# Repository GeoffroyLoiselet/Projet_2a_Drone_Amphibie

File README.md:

# Projet_2a_Drone_Amphibie
Projet drone amphibie ENSEA 2ème année

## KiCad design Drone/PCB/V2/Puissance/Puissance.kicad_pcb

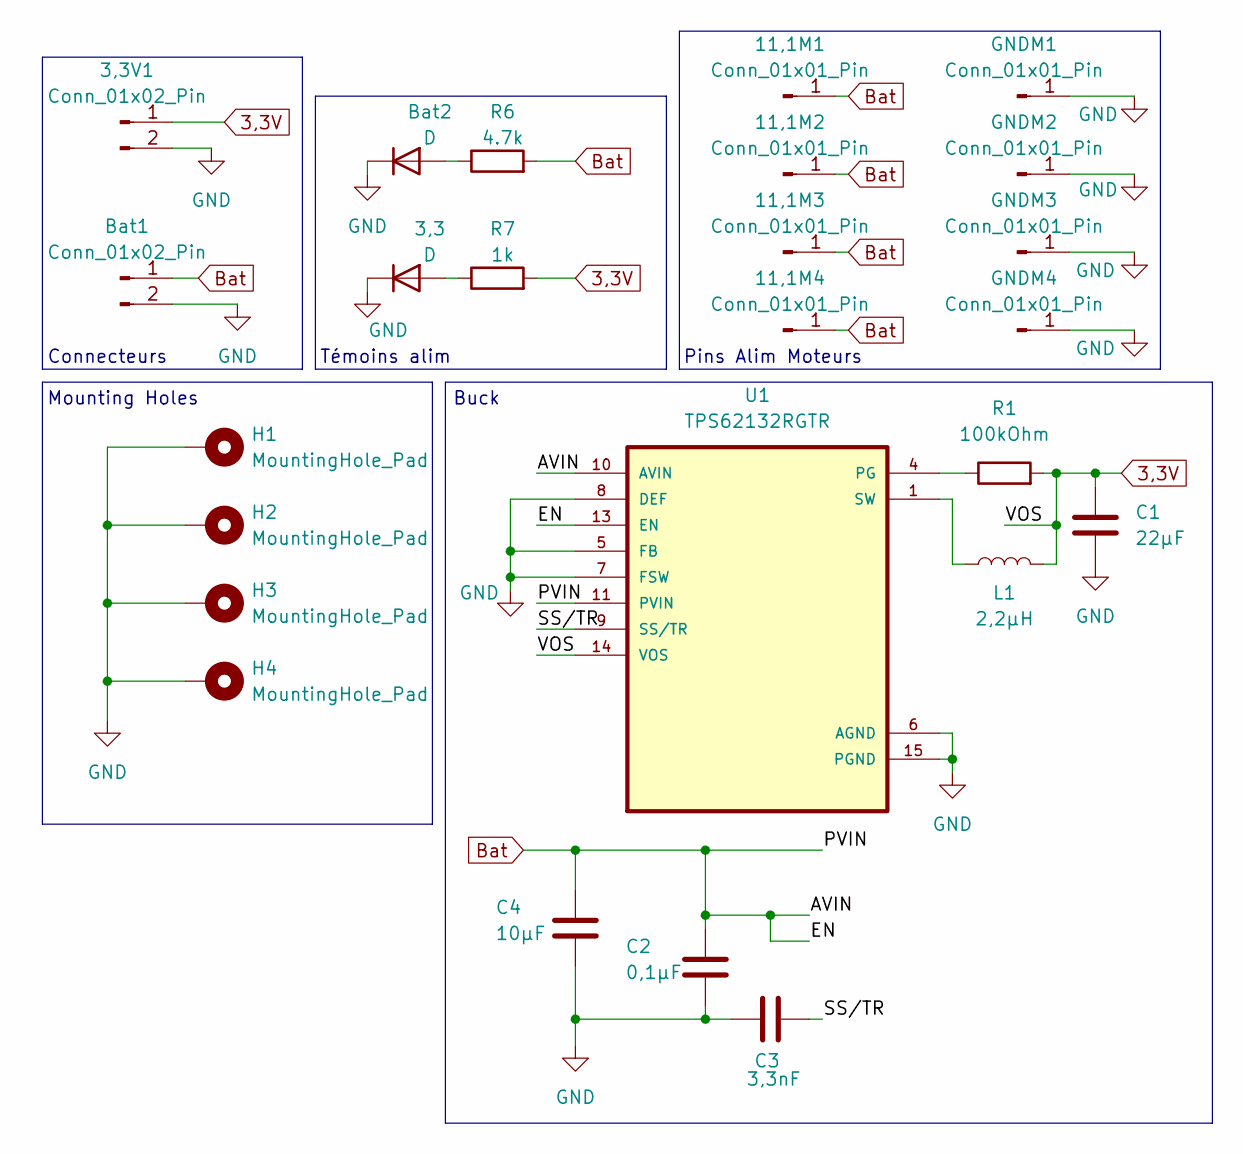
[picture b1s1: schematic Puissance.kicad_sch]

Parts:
3,3: D; D_0603_1608Metric_Pad1.05x0.95mm_HandSolder
3,3V1: Conn_01x02_Pin; PinSocket_1x02_P2.54mm_Vertical
11,1M1, 11,1M2, 11,1M3, 11,1M4: Conn_01x01_Pin; SolderWire-1.5sqmm_1x01_D1.7mm_OD3mm
Bat1: Conn_01x02_Pin; SolderWire-1.5sqmm_1x02_P6mm_D1.7mm_OD3mm
Bat2: D; D_0603_1608Metric_Pad1.05x0.95mm_HandSolder
C1: 22µF; C_0603_1608Metric_Pad1.08x0.95mm_HandSolder
C2: 0,1µF; C_0603_1608Metric_Pad1.08x0.95mm_HandSolder
C3: 3,3nF; C_0603_1608Metric_Pad1.08x0.95mm_HandSolder
C4: 10µF; C_0603_1608Metric_Pad1.08x0.95mm_HandSolder
GNDM1, GNDM2, GNDM3, GNDM4: Conn_01x01_Pin; SolderWire-1.5sqmm_1x01_D1.7mm_OD3mm
H1, H2, H3, H4: MountingHole_Pad; MountingHole_3.2mm_M3_DIN965_Pad
L1: 2,2µH; L_0603_1608Metric_Pad1.05x0.95mm_HandSolder
R1: 100kOhm; R_0201_0603Metric_Pad0.64x0.40mm_HandSolder
R6: 4.7k; R_0603_1608Metric_Pad0.98x0.95mm_HandSolder
R7: 1k; R_0603_1608Metric_Pad0.98x0.95mm_HandSolder
U1: TPS62132RGTR; VQFN-16-1EP_3x3mm_P0.5mm_EP1.1x1.1mm_ThermalVias

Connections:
3,3V: 3,3V1.1, C1.1, L1.2, R1.2, R7.2, U1.14 (VOS)
/SS/TR: C3.2, U1.9 (SS/TR)
Bat: 11,1M1.1, 11,1M2.1, 11,1M3.1, 11,1M4.1, Bat1.1, C2.1, C4.1, R6.2, U1.10 (AVIN), U1.11 (PVIN), U1.12 (PVIN), U1.13 (EN)
GND: 3,3.1 (K), 3,3V1.2, Bat1.2, Bat2.1 (K), C1.2, C2.2, C3.1, C4.2, GNDM1.1, GNDM2.1, GNDM3.1, GNDM4.1, H1.1, H2.1, H3.1, H4.1, U1.5 (FB), U1.6 (AGND), U1.7 (FSW), U1.8 (DEF), U1.15 (PGND), U1.16 (PGND), U1.17 (PGND)
unnamed: 3,3.2 (A), R7.1
unnamed: Bat2.2 (A), R6.1
unnamed: L1.1, U1.1 (SW), U1.2 (SW), U1.3 (SW)
unnamed: R1.1, U1.4 (PG)

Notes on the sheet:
Pins Alim Moteurs
Connecteurs
Buck
Mounting Holes
Témoins alim

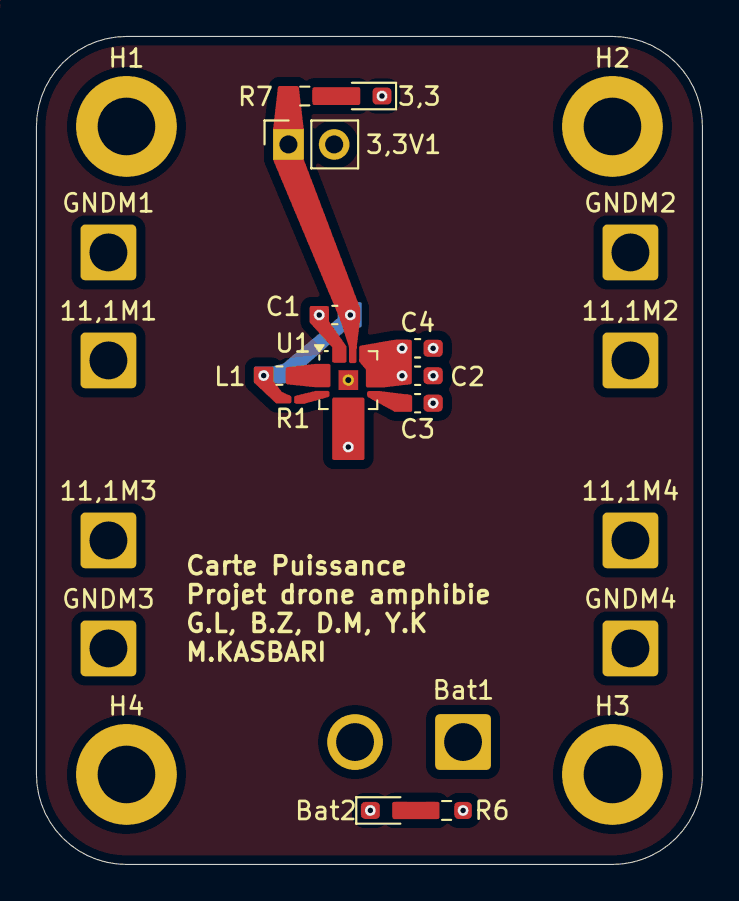
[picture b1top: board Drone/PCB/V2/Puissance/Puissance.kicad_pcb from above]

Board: 4 copper layers, 37.0 x 46.0 mm, 25 parts (0 on the bottom side), 8 nets.

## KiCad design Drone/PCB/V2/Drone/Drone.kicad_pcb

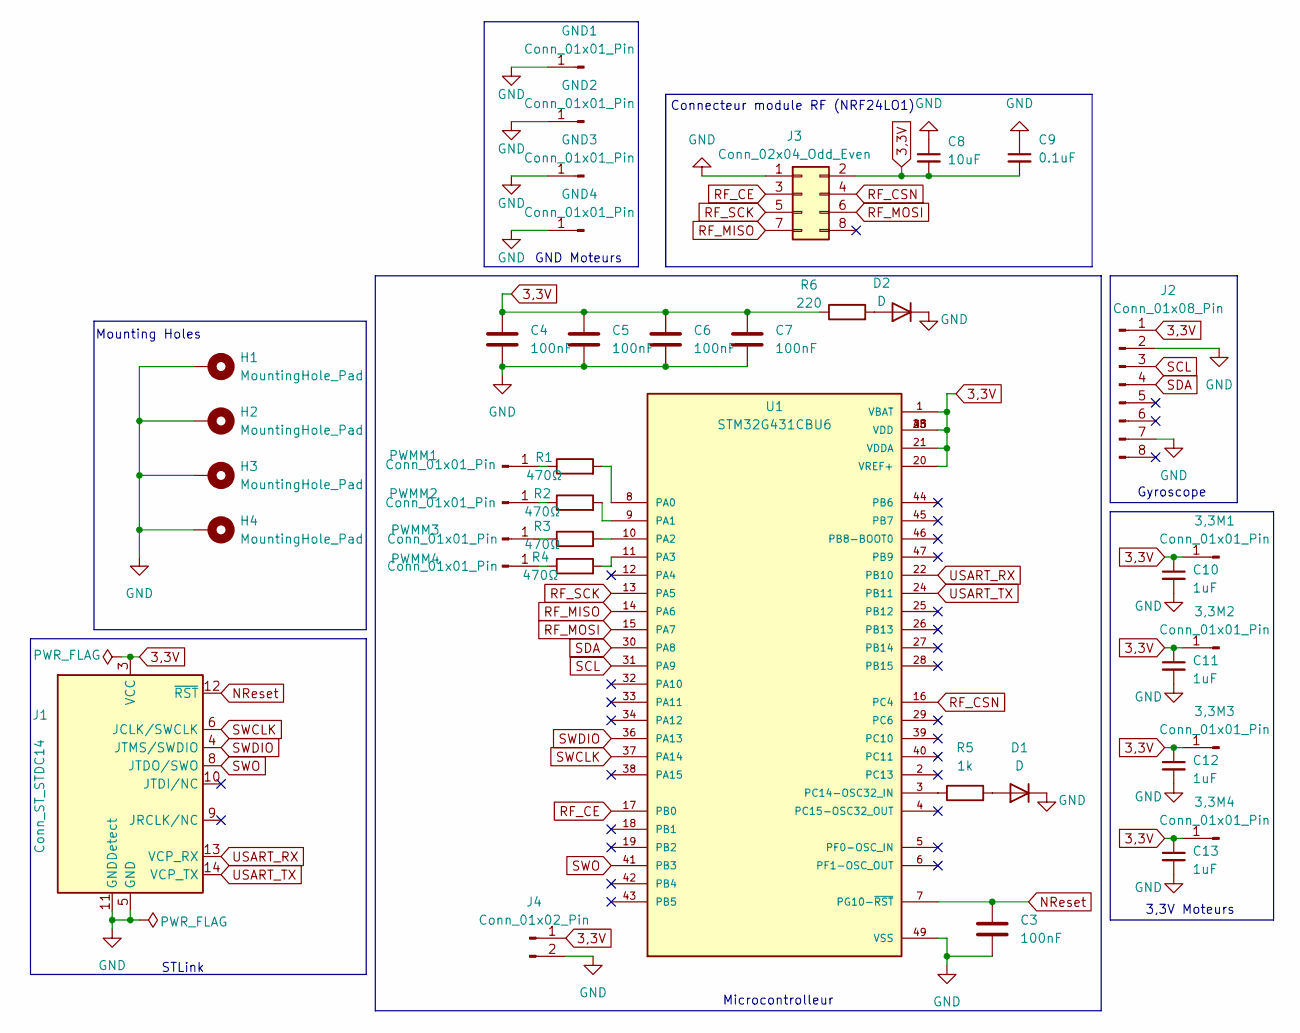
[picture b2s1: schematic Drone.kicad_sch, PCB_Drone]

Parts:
3,3M1, 3,3M2, 3,3M3, 3,3M4: Conn_01x01_Pin; SolderWire-0.75sqmm_1x01_D1.25mm_OD2.3mm
C3, C4, C5, C6, C7: 100nF; C_0603_1608Metric_Pad1.08x0.95mm_HandSolder
C8: 10uF; C_0603_1608Metric_Pad1.08x0.95mm_HandSolder
C9: 0.1uF; C_0603_1608Metric_Pad1.08x0.95mm_HandSolder
C10, C11, C12, C13: 1uF; C_0603_1608Metric_Pad1.08x0.95mm_HandSolder
D1, D2: D; D_0603_1608Metric_Pad1.05x0.95mm_HandSolder
GND1, GND2, GND3, GND4: Conn_01x01_Pin; SolderWire-0.75sqmm_1x01_D1.25mm_OD2.3mm
H1, H2, H3, H4: MountingHole_Pad; MountingHole_3.2mm_M3_DIN965_Pad
J1: Conn_ST_STDC14; PinHeader_2x07_P1.27mm_Vertical_SMD
J2: Conn_01x08_Pin; PinSocket_1x08_P1.00mm_Vertical
J3: Conn_02x04_Odd_Even; JST_PHD_B8B-PHDSS_2x04_P2.00mm_Vertical
J4: Conn_01x02_Pin; PinSocket_1x02_P2.54mm_Vertical
PWMM1, PWMM2, PWMM3, PWMM4: Conn_01x01_Pin; SolderWire-0.75sqmm_1x01_D1.25mm_OD2.3mm
R1, R2, R3, R4: 470Ω; R_0603_1608Metric_Pad0.98x0.95mm_HandSolder
R5: 1k; R_0603_1608Metric_Pad0.98x0.95mm_HandSolder
R6: 220; R_0603_1608Metric_Pad0.98x0.95mm_HandSolder
U1: STM32G431CBU6; QFN50P700X700X60-49N; PARTREV 6

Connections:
3,3V: 3,3M1.1, 3,3M2.1, 3,3M3.1, 3,3M4.1, C4.1, C5.1, C6.1, C7.1, C8.2, C9.2, C10.1, C11.1, C12.1, C13.1, J1.3 (VCC), J2.1, J3.2, J4.1, R6.1, U1.1 (VBAT), U1.20 (VREF+), U1.21 (VDDA), U1.23 (VDD), U1.35 (VDD), U1.48 (VDD)
GND: C3.2, C4.2, C5.2, C6.2, C7.2, C8.1, C9.1, C10.2, C11.2, C12.2, C13.2, D1.1 (K), D2.1 (K), GND1.1, GND2.1, GND3.1, GND4.1, H1.1, H2.1, H3.1, H4.1, J1.5 (GND), J1.7 (GND), J1.11 (GNDDetect), J2.2, J2.7, J3.1, J4.2, U1.49 (VSS)
NReset: C3.1, J1.12 (~RST), U1.7 (PG10-~RST)
unnamed: D1.2 (A), R5.2
unnamed: D2.2 (A), R6.2
unnamed: PWMM1.1, R1.1
unnamed: PWMM2.1, R2.1
unnamed: PWMM3.1, R3.1
unnamed: PWMM4.1, R4.1
unnamed: R1.2, U1.8 (PA0)
unnamed: R2.2, U1.9 (PA1)
unnamed: R3.2, U1.10 (PA2)
unnamed: R4.2, U1.11 (PA3)
unnamed: R5.1, U1.3 (PC14-OSC32_IN)
RF_CE: J3.3, U1.17 (PB0)
RF_CSN: J3.4, U1.16 (PC4)
RF_MISO: J3.7, U1.14 (PA6)
RF_MOSI: J3.6, U1.15 (PA7)
RF_SCK: J3.5, U1.13 (PA5)
SCL: J2.3, U1.31 (PA9)
SDA: J2.4, U1.30 (PA8)
SWCLK: J1.6 (JCLK/SWCLK), U1.37 (PA14)
SWDIO: J1.4 (JTMS/SWDIO), U1.36 (PA13)
SWO: J1.8 (JTDO/SWO), U1.41 (PB3)
USART_RX: J1.13 (VCP_RX), U1.22 (PB10)
USART_TX: J1.14 (VCP_TX), U1.24 (PB11)

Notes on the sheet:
3,3V Moteurs
Connecteur module RF (NRF24LO1)
Microcontrolleur
Gyroscope
STLink
Mounting Holes
GND Moteurs

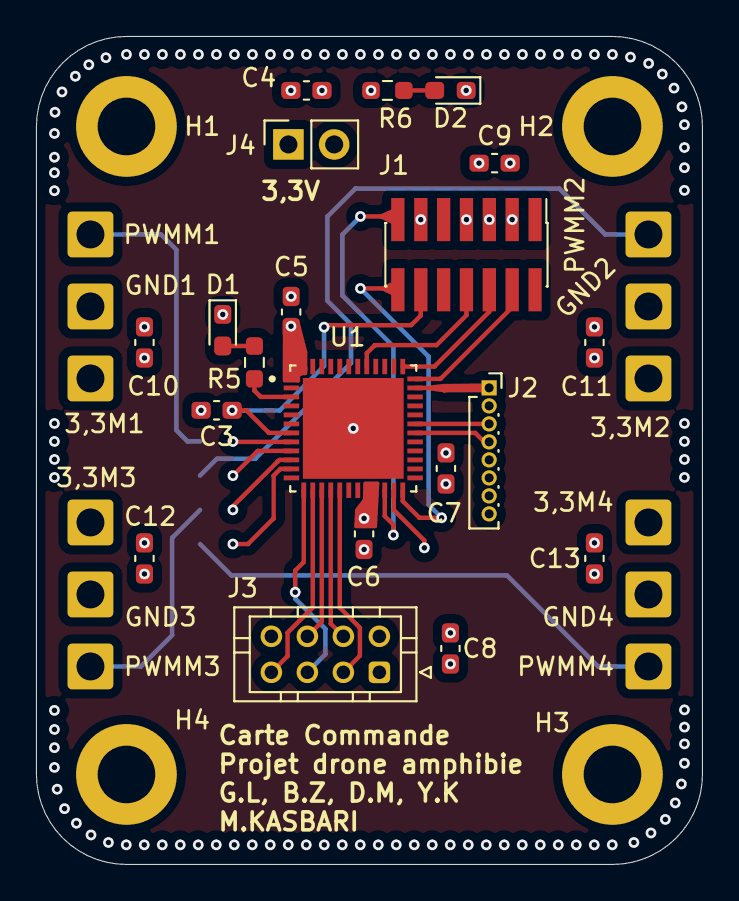
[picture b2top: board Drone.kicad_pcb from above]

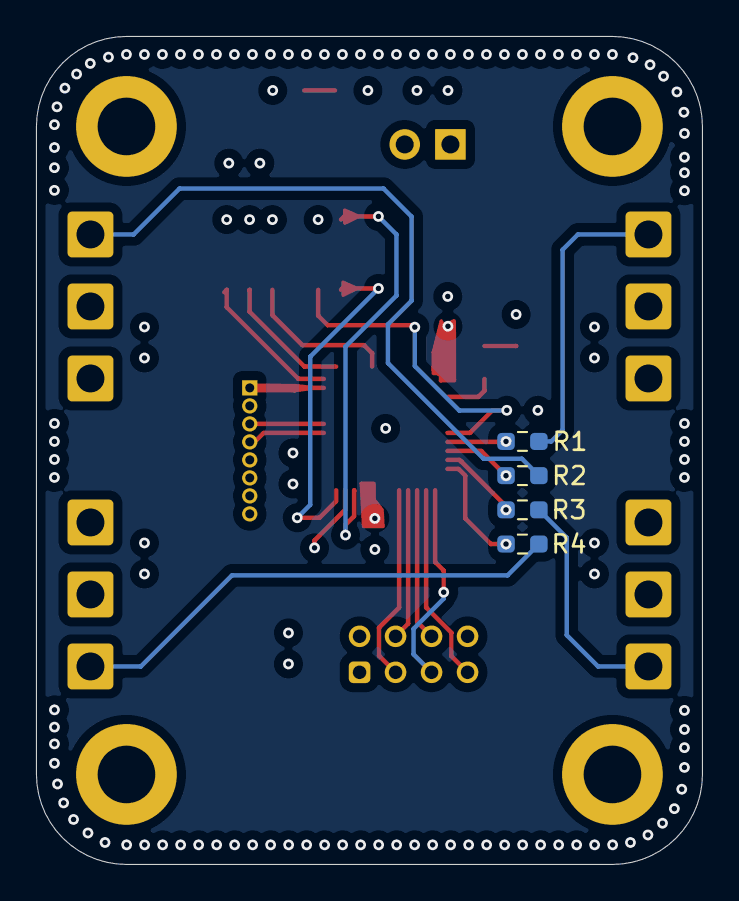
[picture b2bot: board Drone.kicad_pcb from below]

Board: 4 copper layers, 37.0 x 46.0 mm, 40 parts (4 on the bottom side), 26 nets.

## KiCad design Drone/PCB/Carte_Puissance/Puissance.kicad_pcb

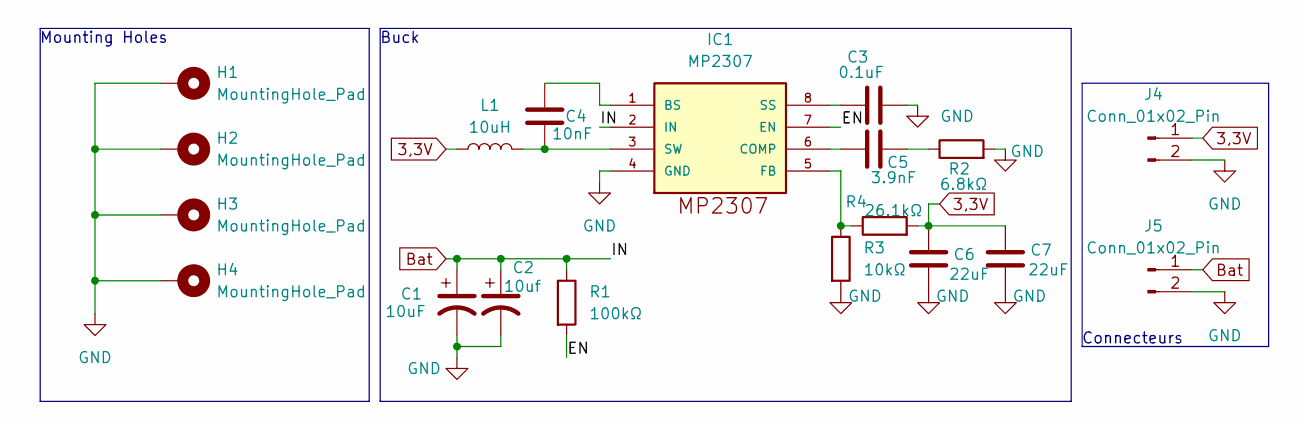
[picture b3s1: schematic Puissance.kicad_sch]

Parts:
C1: 10uF; C_0603_1608Metric_Pad1.08x0.95mm_HandSolder
C2: 10uf; C_0603_1608Metric_Pad1.08x0.95mm_HandSolder
C3: 0.1uF; C_0603_1608Metric_Pad1.08x0.95mm_HandSolder
C4: 10nF; C_0603_1608Metric_Pad1.08x0.95mm_HandSolder
C5: 3.9nF; C_0603_1608Metric_Pad1.08x0.95mm_HandSolder
C6, C7: 22uF; C_0603_1608Metric_Pad1.08x0.95mm_HandSolder
H1, H2, H3, H4: MountingHole_Pad; MountingHole_3.2mm_M3_DIN965_Pad
IC1: MP2307; MP2307DN
J4, J5: Conn_01x02_Pin; PinSocket_1x02_P2.54mm_Vertical
L1: 10uH; L_0603_1608Metric_Pad1.05x0.95mm_HandSolder
R1: 100kΩ; R_0603_1608Metric_Pad0.98x0.95mm_HandSolder
R2: 6.8kΩ; R_0603_1608Metric_Pad0.98x0.95mm_HandSolder
R3: 10kΩ; R_0603_1608Metric_Pad0.98x0.95mm_HandSolder
R4: 26.1kΩ; R_0603_1608Metric_Pad0.98x0.95mm_HandSolder

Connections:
3,3V: C6.1, C7.1, J4.1, L1.1, R4.2
/EN: IC1.7 (EN), R1.2
Bat: C1.1, C2.1, IC1.2 (IN), J5.1, R1.1
GND: C1.2, C2.2, C3.2, C6.2, C7.2, H1.1, H2.1, H3.1, H4.1, IC1.4 (GND), IC1.9, J4.2, J5.2, R2.2, R3.2
unnamed: C5.2, R2.1
unnamed: C4.2, IC1.1 (BS)
unnamed: C5.1, IC1.6 (COMP)
unnamed: IC1.5 (FB), R3.1, R4.1
unnamed: C3.1, IC1.8 (SS)
unnamed: C4.1, IC1.3 (SW), L1.2

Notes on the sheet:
Connecteurs
Buck
Mounting Holes

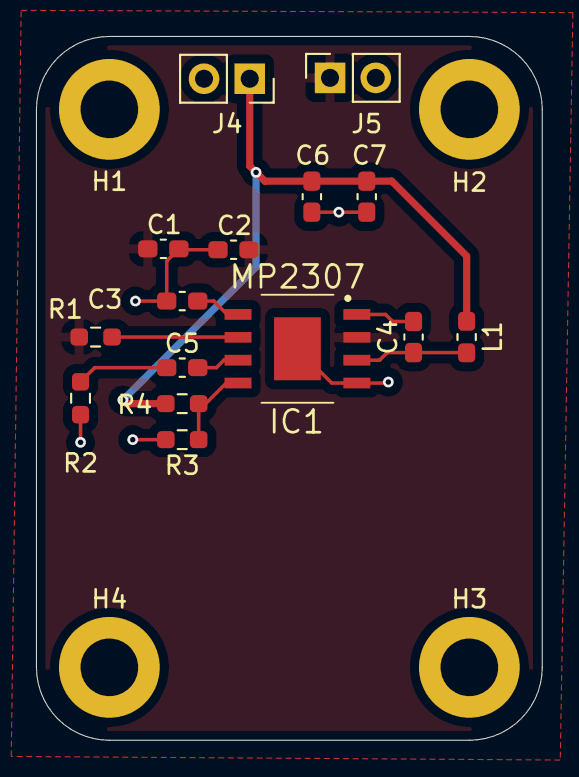
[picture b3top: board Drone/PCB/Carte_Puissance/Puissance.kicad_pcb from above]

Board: 2 copper layers, 28.1 x 39.1 mm, 19 parts (0 on the bottom side), 10 nets.

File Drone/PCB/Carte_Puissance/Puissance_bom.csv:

"Id";"Référence";"Empreinte";"Quantité";"Désignation";"Fournisseur et réf";
1;"J4,J5";"PinSocket_1x02_P2.54mm_Vertical";2;"Conn_01x02_Pin";;;
2;"IC1";"MP2307DN";1;"MP2307";;;
3;"C5";"C_0603_1608Metric_Pad1.08x0.95mm_HandSolder";1;"3.9nF";;;
4;"R2";"R_0603_1608Metric_Pad0.98x0.95mm_HandSolder";1;"6.8kΩ";;;
5;"C3";"C_0603_1608Metric_Pad1.08x0.95mm_HandSolder";1;"0.1uF";;;
6;"R4";"R_0603_1608Metric_Pad0.98x0.95mm_HandSolder";1;"26.1kΩ";;;
7;"C1";"C_0603_1608Metric_Pad1.08x0.95mm_HandSolder";1;"10uF";;;
8;"C4";"C_0603_1608Metric_Pad1.08x0.95mm_HandSolder";1;"10nF";;;
9;"R3";"R_0603_1608Metric_Pad0.98x0.95mm_HandSolder";1;"10kΩ";;;
10;"C2";"C_0603_1608Metric_Pad1.08x0.95mm_HandSolder";1;"10uf";;;
11;"R1";"R_0603_1608Metric_Pad0.98x0.95mm_HandSolder";1;"100kΩ";;;
12;"C7,C6";"C_0603_1608Metric_Pad1.08x0.95mm_HandSolder";2;"22uF";;;
13;"L1";"L_0603_1608Metric_Pad1.05x0.95mm_HandSolder";1;"10uH";;;

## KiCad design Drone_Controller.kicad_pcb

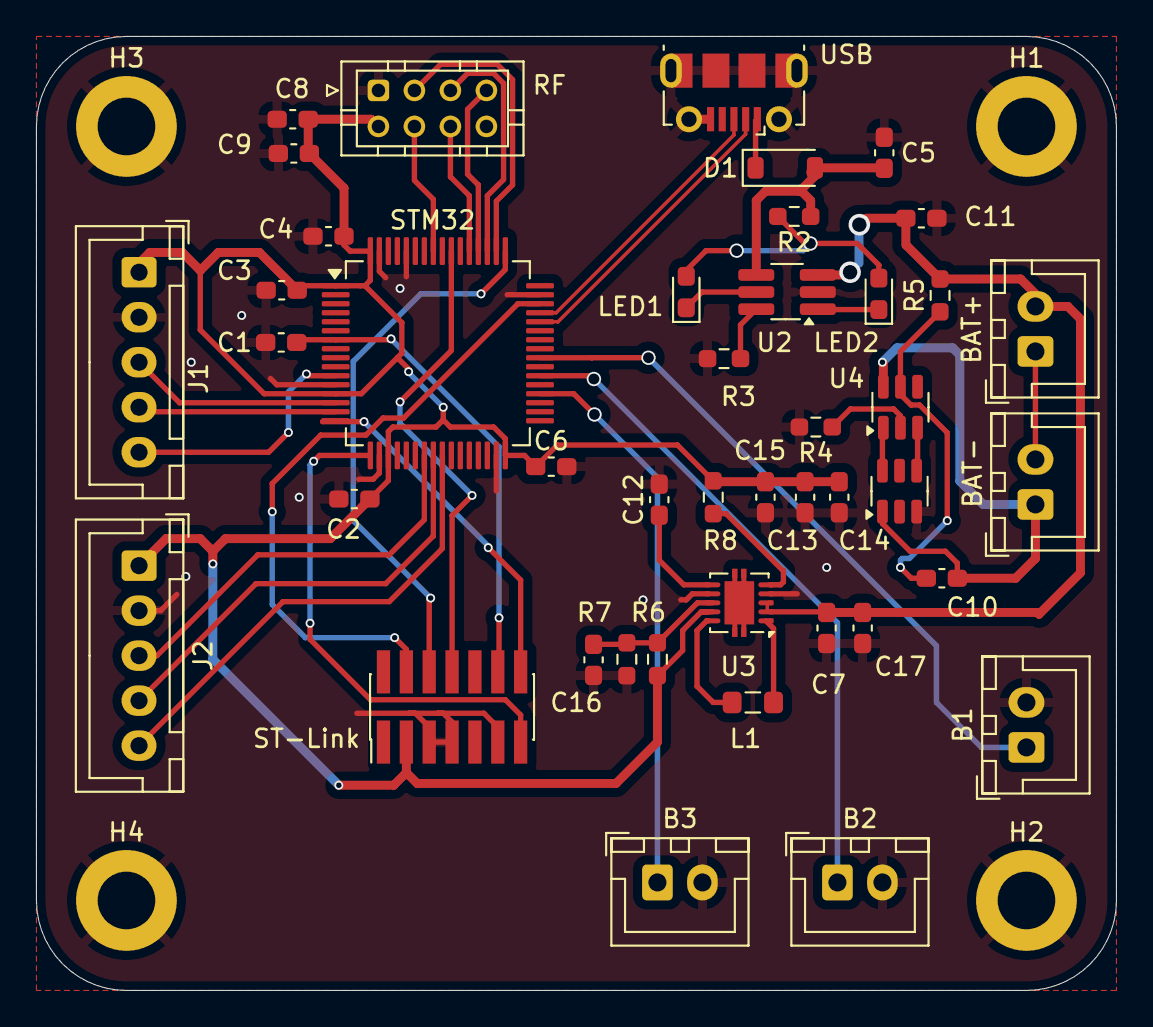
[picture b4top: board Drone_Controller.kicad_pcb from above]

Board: 2 copper layers, 60.0 x 53.0 mm, 47 parts (0 on the bottom side), 42 nets.

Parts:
B1, B2, B3: Conn_01x02_Socket; JST_XH_B2B-XH-A_1x02_P2.50mm_Vertical
BAT+: Conn_01x02_Socket; JST_XH_B2B-XH-A_1x02_P2.50mm_Vertical
BAT-: Conn_01x02_Socket; JST_XH_B2B-XH-A_1x02_P2.50mm_Vertical
C1, C2, C3, C4, C6: 100nF; C_0603_1608Metric_Pad1.08x0.95mm_HandSolder
C5: 2.2uF; C_0603_1608Metric_Pad1.08x0.95mm_HandSolder
C7, C8, C17: 10uF; C_0603_1608Metric_Pad1.08x0.95mm_HandSolder
C9, C10, C12: 0.1uF; C_0603_1608Metric_Pad1.08x0.95mm_HandSolder
C11: C_Small; C_0603_1608Metric_Pad1.08x0.95mm_HandSolder
C13, C14, C15: 22uF; C_0603_1608Metric_Pad1.08x0.95mm_HandSolder
C16: 10pF; C_0603_1608Metric_Pad1.08x0.95mm_HandSolder
D1: D_Small; D_SOD-123
H1, H2, H3, H4: MountingHole_Pad; MountingHole_3.2mm_M3_DIN965_Pad
J1, J2: Conn_01x05_Pin; JST_XH_B5B-XH-A_1x05_P2.50mm_Vertical
L1: 1uH; L_0805_2012Metric_Pad1.05x1.20mm_HandSolder
LED1, LED2: LED_Small; LED_0603_1608Metric_Pad1.05x0.95mm_HandSolder
R2: 330; R_0603_1608Metric_Pad0.98x0.95mm_HandSolder
R3: R_PRG; R_0603_1608Metric_Pad0.98x0.95mm_HandSolder
R4, R6, R7: R_Small; R_0603_1608Metric_Pad0.98x0.95mm_HandSolder
R5: 100; R_0603_1608Metric_Pad0.98x0.95mm_HandSolder
R8: 1M; R_0603_1608Metric_Pad0.98x0.95mm_HandSolder
RF: Conn_02x04_Odd_Even; JST_PHD_B8B-PHDSS_2x04_P2.00mm_Vertical
ST-Link: Conn_ST_STDC14; PinHeader_2x07_P1.27mm_Vertical_SMD
STM32: STM32L476RGTx; LQFP-64_10x10mm_P0.5mm
U2: TP4057; TSOT-23-6_HandSoldering
U3: TPS63060DSCR; Texas_DSC0010J
U4: DW01A; SOT-23-6
U5: 8205A; SOT-23-6
USB: USB_B_Micro; USB_Micro-B_Molex-105017-0001

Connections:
+3.3V: C2.1, C3.1, C4.1, C6.1, C8.2, C9.2, C13.1, C14.1, C15.1, J1.1, J2.1, R6.1, R8.2, RF.2, ST-Link.3 (VCC), STM32.1 (VBAT), STM32.13 (VDDA), STM32.19 (VDD), STM32.32 (VDD), STM32.64 (VDD), U3.9 (VOUT)
+5V: C5.2, D1.2 (A), R2.1, U2.4 (VCC)
BAT+: BAT+.2, C7.1, C11.2, C17.1, R5.2, U2.3 (BAT), U3.2 (VIN), U3.3 (EN)
BAT-: BAT-.1, C10.2, U4.6 (GND), U5.1
Button1: B1.1, STM32.40 (PC9)
Button2: B2.1, STM32.38 (PC7)
Button3: B3.1, STM32.36 (PB15)
FB: C16.1, R6.2, R7.1, U3.8 (FB)
GND: B1.2, B2.2, B3.2, C1.2, C2.2, C3.2, C4.2, C5.1, C6.2, C7.2, C8.1, C9.1, C11.1, C12.2, C13.2, C14.2, C15.2, C16.2, C17.2, H1.1, H2.1, H3.1, H4.1, J1.2, J2.2, R3.1, R4.2, R7.2, RF.1, ST-Link.5 (GND), ST-Link.7 (GND), ST-Link.11 (GNDDetect), STM32.12 (VSSA), STM32.18 (VSS), STM32.31 (VSS), STM32.47 (VSS), STM32.60 (BOOT0), STM32.63 (VSS), U2.2 (GND), U3.4 (PS/SYNC), U3.7 (GND), U5.3, USB.5 (GND), USB.6 (Shield)
Joystick1_switch: J1.5, STM32.11 (PC3)
Joystick1_x: J1.3, STM32.14 (PA0)
Joystick1_y: J1.4, STM32.15 (PA1)
Joystick2_switch: J2.5, STM32.25 (PC5)
Joystick2_x: J2.3, STM32.23 (PA7)
Joystick2_y: J2.4, STM32.24 (PC4)
NRST: C1.1, ST-Link.12 (~RST), STM32.7 (NRST)
unnamed: D1.1 (K), USB.1 (VBUS)
unnamed: LED1.2 (A), LED2.2 (A), R2.2
unnamed: LED2.1 (K), U2.1 (~CHRG)
unnamed: LED1.1 (K), U2.5 (~STDBY)
unnamed: BAT+.1, BAT-.2
unnamed: R3.2, U2.6 (PROG)
unnamed: L1.2, U3.1 (L1)
unnamed: L1.1, U3.10 (L2)
unnamed: R8.1, U3.5 (PG)
unnamed: C12.1, U3.6 (VAUX)
unnamed: R4.1, U4.2 (CS)
unnamed: U4.3 (OC), U5.4
unnamed: U4.1 (OD), U5.6
unnamed: C10.1, R5.1, U4.5 (VCC)
RF_CE: RF.3, STM32.50 (PA15)
RF_CSN: RF.4, STM32.57 (PB5)
RF_MISO: RF.7, STM32.52 (PC11)
RF_MOSI: RF.6, STM32.53 (PC12)
RF_SCK: RF.5, STM32.51 (PC10)
SWCLK: ST-Link.6 (JCLK/SWCLK), STM32.49 (PA14)
SWDIO: ST-Link.4 (JTMS/SWDIO), STM32.46 (PA13)
SWO: ST-Link.8 (JTDO/SWO), STM32.55 (PB3)
USART_RX: ST-Link.13 (VCP_RX), STM32.17 (PA3)
USART_TX: ST-Link.14 (VCP_TX), STM32.16 (PA2)
USB_D+: STM32.45 (PA12), USB.3 (D+)
USB_D-: STM32.44 (PA11), USB.2 (D-)

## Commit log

2025-09-30 Programme pour STM32 fonctionnement moteur
2025-09-30 Create x
2025-09-30 Create Avancées 30 sept
2025-10-07 Create drone_book
2025-10-07 Create Article_sur_drone_amphibie
2025-10-07 Rename Article_sur_drone_amphibie to Article_sur_la_conception_de_drone_amphibie
2025-10-07 Create Code qui affiche gyro+accelerometre
2025-11-18 Rename MP2307buck.pdf to Drone/MP2307buck.pdf
2025-11-18 Create Datasheet
2025-11-18 Create PCB
2025-11-18 Rename Drone_Controller.kicad_pcb to Manette/PCB/Drone_Controller.kicad_pcb
2025-11-18 Rename Drone_Controller.kicad_sch to Manette/PCB/Drone_Controller.kicad_sch
2025-11-18 Create uozdf
2025-11-18 Rename Drone/MP2307buck.pdf to Drone/Datasheet/MP2307buck.pdf
2025-11-18 Create oiyd
2025-11-18 Rename Article_sur_la_conception_de_drone_amphibie to Drone/ressources/Article_sur_la_conception_de_drone_amphibie
2025-11-18 Rename Projet_2A_LAINE_PICHON.zip to Drone/ressources/Projet_2A_LAINE_PICHON.zip
2025-11-18 Rename BLDC_Motor_and_propeller_selection_for_autonomous_amphibious_drones.pdf to Drone/ressources/BLDC_Motor_and_propeller_selection_for_autonomous_amphibious_drones.pdf
2025-11-18 Rename flight_controler_drone_article.pdf to Drone/ressources/flight_controler_drone_article.pdf
2025-11-18 Rename cr projet BRAMI BOULARD.pdf to Drone/ressourcescr projet BRAMI BOULARD.pdf
2025-11-18 Rename Yaw_Axis_Corrected.svg.png to Drone/ressources/Yaw_Axis_Corrected.svg.png
2025-11-18 Rename drone_book to Drone/ressources/drone_book
2025-11-18 Rename anleitung schnurzz regler EN.pdf to Drone/ressources/anleitung schnurzz regler EN.pdf
2025-11-18 Rename comment-piloter-un-drone-fpv-throttle-yaw-pitch-roll-lacet-tangage-roulis-accelerateur-mode-2.jpg to Drone/comprendre/comment-piloter-un-drone-fpv-throttle-yaw-pitch-roll-lacet-tangage-roulis-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
2025-11-18 Rename Yaw_Axis_Corrected.svg.png to Yaw_Axis_Corrected.svg.png
2025-11-18 Rename Moteur BLDC and propellers.docx to Drone/Datasheet/Moteur BLDC and propellers.docx
2025-11-18 Rename tests_projet.zip to Drone/ressources/tests_projet.zip
2025-12-09 Rename teort.txt to TXT.txt
2025-12-09 Add usage warning for nrf24l01
    Added warning and usage instructions for nrf24l01.
2025-12-19 Add motor usage instructions to Utilisation.txt
    Added usage instructions for the motor including power supply and PWM settings.
2026-01-14 Create zert
2026-01-20 Add files via upload
    un video pour mieux comprendre : https://youtu.be/rQGIqen2qxA
2026-02-03 psc.txt
2026-02-17 Create V2
2026-02-17 nouveau main.c pour le nrf24 RX
    permet de lire le message envoyé (+ affichage led) mode privilégié de lecture = puTTY en serial com5
